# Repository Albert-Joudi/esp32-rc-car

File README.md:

# esp32-rc-car

## Overview
The **esp32-rc-car** is a custom-built RC car controlled via Bluetooth Low Energy (BLE) using an ESP32 microcontroller. The vehicle is operated from a smartphone through the Dabble app, which provides a virtual game controller interface. The project combines embedded programming, custom PCB design, motor control, and hardware debugging.

---

## Project Media

▶ Watch the ESP32 RC Car features showcase: https://youtube.com/shorts/to-kIwxq354?si=jSNwVrnpMwx3RoQd 

▶ Watch the full demo video of the ESP32 RC Car: https://youtube.com/shorts/JepBfLC0xiw?si=qRIe9IqqiM_V_Yjg

---

## Features
- BLE-based wireless control using the ESP32
- Smartphone control via the Dabble app game controller
- Start/Stop system similar to a real car ignition
- DC motor for forward and reverse motion
- Servo motor for left and right steering
- Front headlights and rear taillights
- Direction-based lighting:
  - Front LEDs activate when moving forward
  - Rear LEDs activate when reversing
- Turn signals and hazard lights with dedicated controls
- Horn functionality using a speaker
- Visual feedback (LED blinking) when starting/stopping the car

---

## Control System
- The ESP32 uses its built-in **Bluetooth Low Energy (BLE)** to communicate with a smartphone.
- The **Dabble mobile app** provides a game controller interface.
- Button presses in the app are mapped in the Arduino IDE to ESP32 GPIO pins.
- GPIO pins control:
  - DC motor
  - Servo motor
  - LEDs
  - Speaker (horn)

---

## Hardware Components
- ESP32 development board
- DC motor (rear-wheel drive)
- Servo motor (front-wheel steering)
- DRV8833 motor driver
- Speaker (horn)
- 4 LEDs:
  - 2 front headlights
  - 2 rear taillights
- Custom-designed PCB
- Power switch
- 3.7V 1100mAh Li-Po battery
- 6V 2400mAh Ni-MH battery pack

---

## Power Architecture
- **Dual power supply design**:
  - **Li-Po battery** powers the ESP32
    - Includes a physical switch to turn the system on/off
  - **Ni-MH battery pack** powers:
    - DC motor
    - Servo motor
    - LEDs
    - Speaker
- Power distribution for peripherals is handled directly on the custom PCB.

---

## PCB Design
- Custom PCB designed using **Autodesk Eagle**
- Fully **through-hole components**
- ESP32 is mounted using **headers** (not soldered directly)
- Designed for easy debugging, modification, and component replacement
- Initial motor driver (L293D) was replaced with a **DRV8833** after testing revealed insufficient motor drive strength

---

## Software & Tools
- Arduino IDE (ESP32 programming)
- Dabble mobile app (BLE controller interface)
- Autodesk Eagle (PCB design)
- Tinkercad (circuit simulation and early testing)
- Multimeter (circuit testing and debugging)

---

## Development & Debugging
- The circuit was first simulated and tested in **Tinkercad** to verify connections, motor control, and LED functionality before creating the custom PCB.  
- Multiple iterations were required to validate motor control and power delivery.  
- Problems encountered and solved:
  - Motor driver (L293D) was too weak → replaced with DRV8833
  - Front wheels initially had too much friction → wrapped tires in tape to reduce friction and allow smooth steering
  - Servo motor was not strong enough initially → adjustments made to wheel friction for smooth turning  
- Circuit simulation, real-world testing, and incremental debugging ensured reliable operation.

---

## Skills Demonstrated
- ESP32 programming and BLE integration
- Custom PCB design and layout
- Through-hole soldering and hardware assembly
- Motor driver integration and control
- Dual power supply management
- Circuit testing and debugging
- Embedded system troubleshooting
- Hardware problem solving and iterative design improvements

## Future Improvements
- Integrate motor driver directly onto PCB
- Add battery voltage monitoring
- better cable management and enclosed design

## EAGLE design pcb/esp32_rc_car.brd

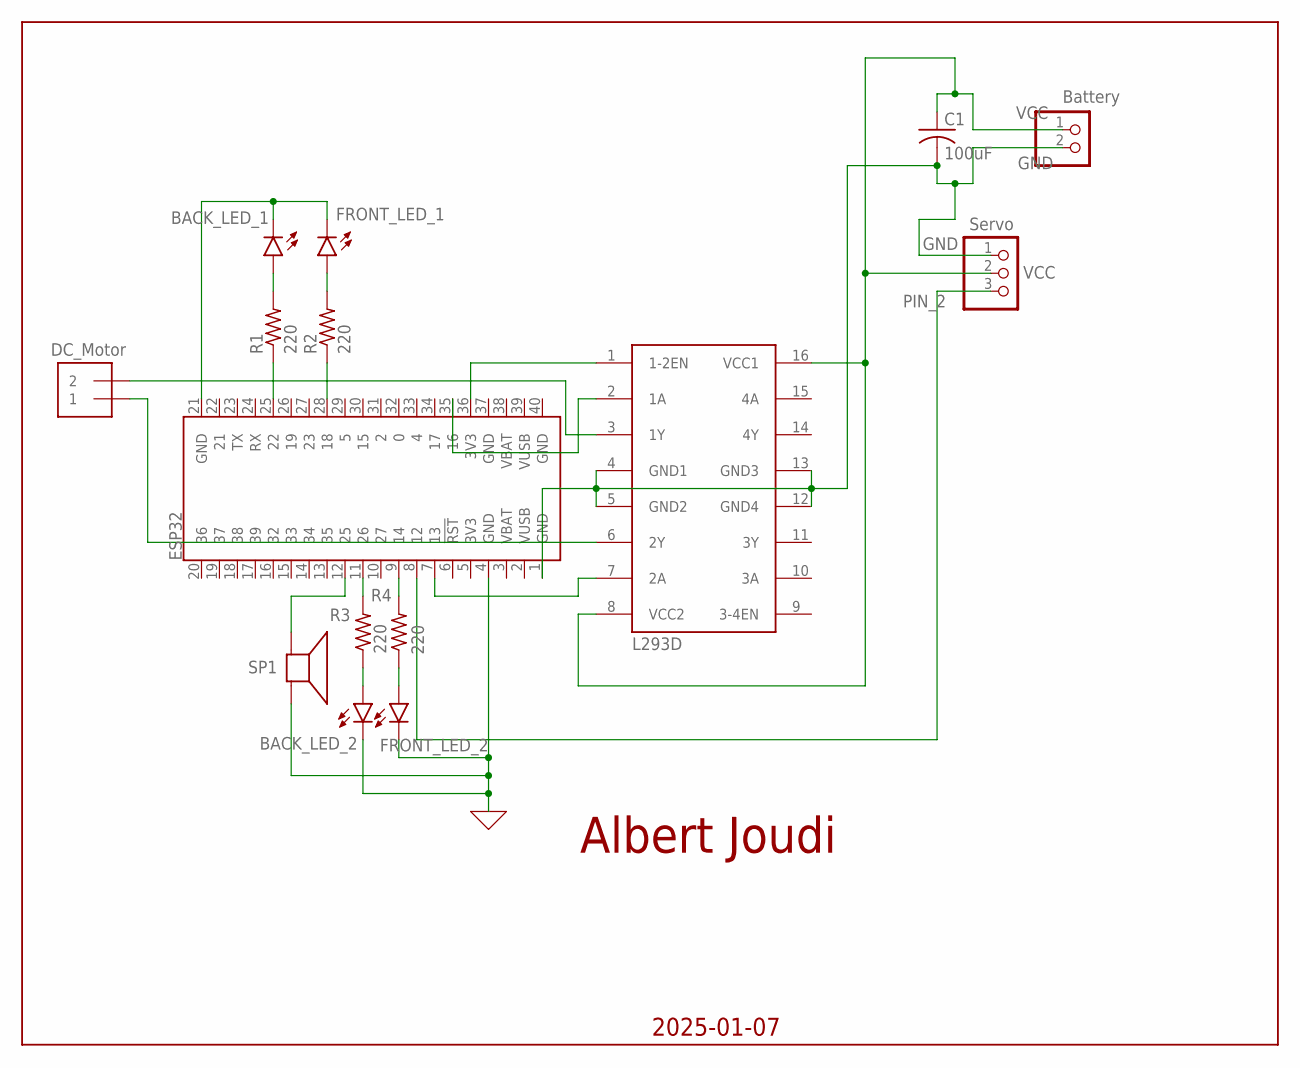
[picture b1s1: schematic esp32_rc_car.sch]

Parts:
BACK_LED_1, BACK_LED_2: LED-5MM-KIT-NO-SILK; LED_5MM-KIT-NO-SILK
BATTERY: PINHD-1X2; 1X02
C1: 100uF; C025-025X050
DC_MOTOR: 1X2-3.5MM
ESP32: ESP32_THING_W_ANT_KEEPOUT; ESP32_THING
FRONT_LED_1, FRONT_LED_2: LED-5MM-KIT-NO-SILK; LED_5MM-KIT-NO-SILK
IC1: L293D; DIL16
R1, R2, R3, R4: 220; 0204/5
SERVO: PINHD-1X3; 1X03
SP1: SPEAKER/AL11P; AL11P

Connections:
0: BACK_LED_2.K (C), ESP32.4 (GND), FRONT_LED_2.K (C), SP1.-
GND: BATTERY.2, C1.2, ESP32.1 (GND), IC1.4 (GND1), IC1.5 (GND2), IC1.12 (GND4), IC1.13 (GND3), SERVO.1
unnamed: ESP32.12 (25), SP1.+
unnamed: ESP32.35 (16), IC1.2 (1A)
unnamed: DC_MOTOR.2, IC1.3 (1Y)
unnamed: DC_MOTOR.1, IC1.6 (2Y)
unnamed: ESP32.7 (13), IC1.7 (2A)
unnamed: BACK_LED_2.A, R3.1
unnamed: ESP32.28 (18), R2.1
unnamed: ESP32.11 (26), R3.2
unnamed: ESP32.25 (22), R1.1
unnamed: ESP32.9 (14), R4.2
unnamed: FRONT_LED_2.A, R4.1
unnamed: ESP32.36 (3V3), IC1.1 (1-2EN)
unnamed: FRONT_LED_1.A, R2.2
unnamed: BACK_LED_1.A, R1.2
unnamed: BACK_LED_1.K (C), ESP32.21 (GND), FRONT_LED_1.K (C)
PIN_2: ESP32.8 (12), SERVO.3
VCC: BATTERY.1, C1.1, IC1.8 (VCC2), IC1.16 (VCC1), SERVO.2

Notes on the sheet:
Albert Joudi
DC_Motor
Battery
Servo
2025-01-07

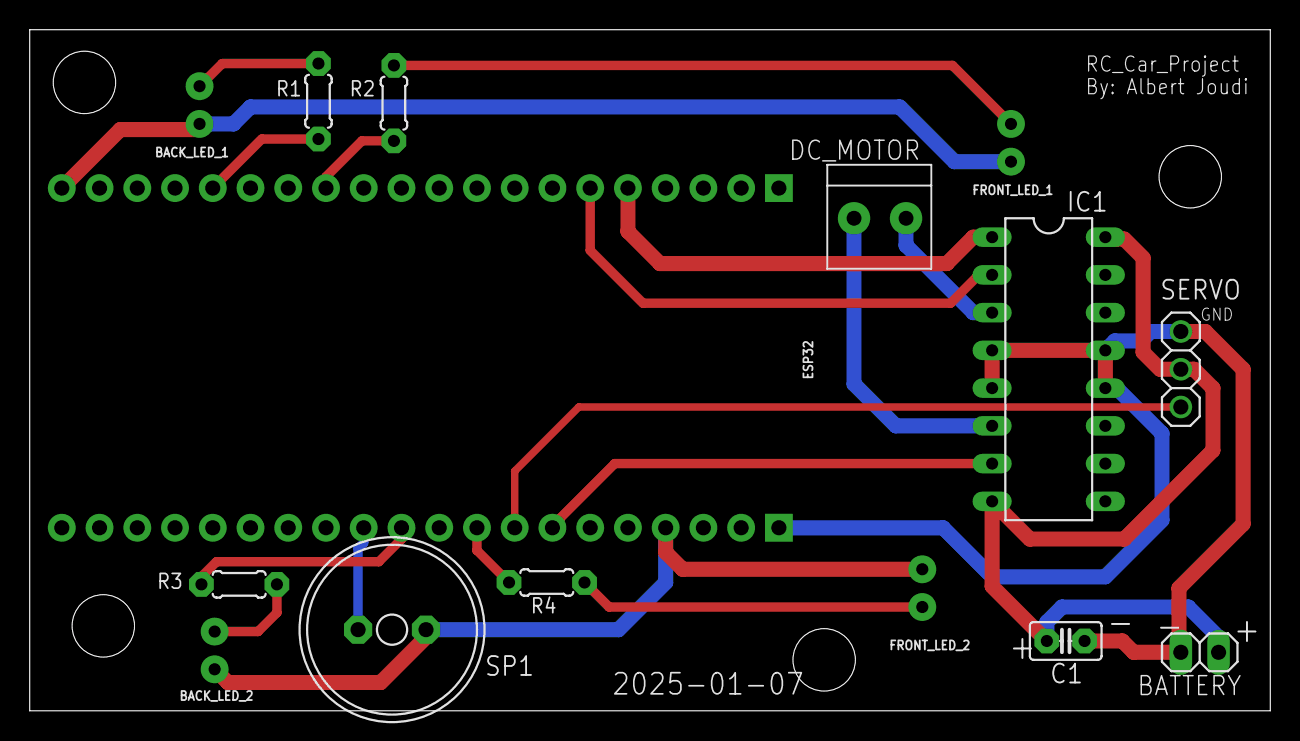
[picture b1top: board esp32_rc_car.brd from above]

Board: 2 copper layers, 83.5 x 45.8 mm, 15 parts (0 on the bottom side), 19 nets.

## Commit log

2026-01-09 Added README.md

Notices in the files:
parts and their libraries:
SparkFun-Boards: Licensing: Creative Commons ShareAlike 4.0 International - https://creativecommons.org/licenses/by-sa/4.0
